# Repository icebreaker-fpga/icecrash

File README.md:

# iCECrash

The Retro game console and demoscene motherboard for iCEBreaker-bitsy.

This project has moved to [Codeberg](https://codeberg.org/icebreaker-fpga/icecrash)

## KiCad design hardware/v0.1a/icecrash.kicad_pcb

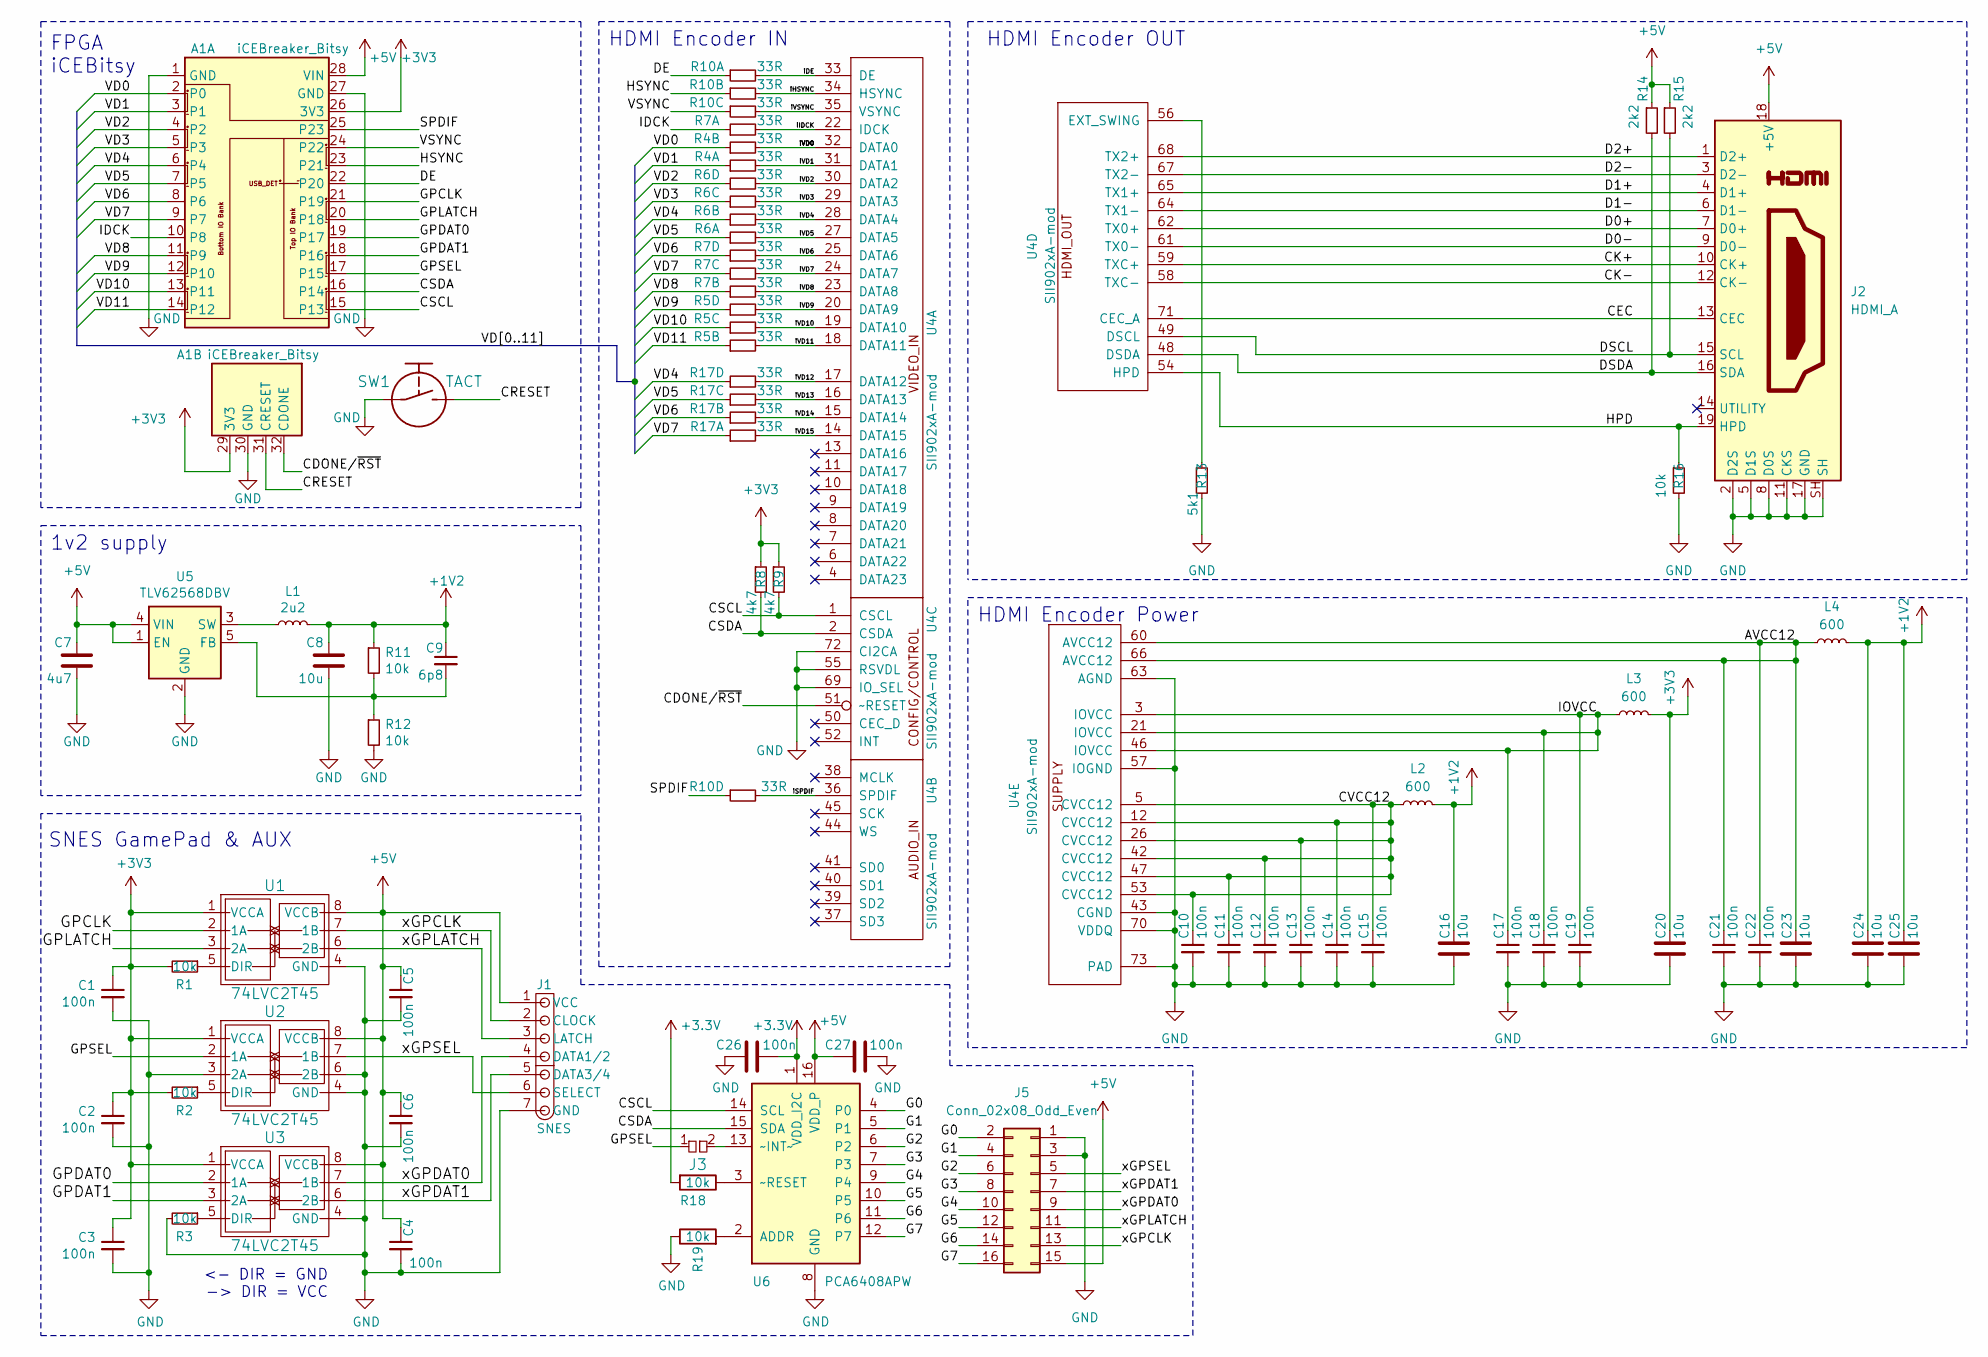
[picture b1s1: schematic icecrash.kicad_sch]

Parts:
A1: iCEBreaker_Bitsy
C1, C2, C3, C4, C5, C6, C10, C11, C12, C13, C14, C15, C17, C18, C19, C21, C22: 100n; C_0402
C7: 4u7; C_0603
C8, C16, C20, C23, C24, C25: 10u; C_0603
C9: 6p8; C_0402
C26, C27: 100n; C_0402_1005Metric; MPN TMK105BJ104KV-F
J1: SNES
J2: HDMI_A; HDMI-10029449-111RLF
J3: pkl_jumper; J_0603
J5: Conn_02x08_Odd_Even; PinHeader_2x08_P2.54mm_Horizontal
L1: 2u2; L_0805
L2, L3, L4: 600; L_0402
R1, R2, R3, R11, R12, R16: 10k; R_0402
R4, R5, R6, R7, R10, R17: 33R; R_Array_Convex_4x0402
R8, R9: 4k7; R_0402
R13: 5k1; R_0402
R14, R15: 2k2; R_0402
R18, R19: 10k; R_0402_1005Metric; MPN RC0402FR-1310KL
SW1: TACT; SW_SPST_3x4x2.5
U1, U2, U3: 74LVC2T45; SOT-833-1
U4: SII902xA-mod; QFN-72-1EP_10x10mm_P0.5mm_EP6x6mm_ThermalVias
U5: TLV62568DBV; SOT-23-5
U6: PCA6408APW; TSSOP-16_4.4x5mm_P0.65mm; MPN PCA6408APW

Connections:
+1V2: C8.1, C9.1, C16.1, C24.1, C25.1, L1.1, L2.1, L4.1, R11.1
+5V: A1.28 (VIN), C4.1, C5.1, C6.1, C7.1, C27.1, J1.1 (VCC), J2.18 (+5V), J5.15, R14.1, R15.1, U1.8 (VCCB), U2.8 (VCCB), U3.8 (VCCB), U5.1 (EN), U5.4 (VIN), U6.16 (VDD_P)
/AVCC12: C21.1, C22.1, C23.1, L4.2, U4.60 (AVCC12), U4.66 (AVCC12)
/CDONE/~RST: A1.32 (CDONE), U4.51 (~RESET)
/CEC: J2.13 (CEC), U4.71 (CEC_A)
/CK+: J2.10 (CK+), U4.59 (TXC+)
/CK-: J2.12 (CK-), U4.58 (TXC-)
/CRESET: A1.31 (CRESET), SW1.2
/CSCL: A1.15 (P13), R9.2, U4.1 (CSCL), U6.14 (SCL)
/CSDA: A1.16 (P14), R8.2, U4.2 (CSDA), U6.15 (SDA)
/CVCC12: C10.1, C11.1, C12.1, C13.1, C14.1, C15.1, L2.2, U4.5 (CVCC12), U4.12 (CVCC12), U4.26 (CVCC12), U4.42 (CVCC12), U4.47 (CVCC12), U4.53 (CVCC12)
/D0+: J2.7 (D0+), U4.62 (TX0+)
/D0-: J2.9 (D0-), U4.61 (TX0-)
/D1+: J2.4 (D1+), U4.65 (TX1+)
/D1-: J2.6 (D1-), U4.64 (TX1-)
/D2+: J2.1 (D2+), U4.68 (TX2+)
/D2-: J2.3 (D2-), U4.67 (TX2-)
/DE: A1.22 (P20), R10.1
/DSCL: J2.15 (SCL), R15.2, U4.49 (DSCL)
/DSDA: J2.16 (SDA), R14.2, U4.48 (DSDA)
/G0: J5.2, U6.4 (P0)
/G1: J5.4, U6.5 (P1)
/G2: J5.6, U6.6 (P2)
/G3: J5.8, U6.7 (P3)
/G4: J5.10, U6.9 (P4)
/G5: J5.12, U6.10 (P5)
/G6: J5.14, U6.11 (P6)
/G7: J5.16, U6.12 (P7)
/GPCLK: A1.21 (P19), U1.2 (1A)
/GPDAT0: A1.19 (P17), U3.2 (1A)
/GPDAT1: A1.18 (P16), U3.3 (2A)
/GPLATCH: A1.20 (P18), U1.3 (2A)
/GPSEL: A1.17 (P15), J3.1, U2.2 (1A)
/HPD: J2.19 (HPD), R16.1, U4.54 (HPD)
/HSYNC: A1.23 (P21), R10.3
/IDCK: A1.10 (P8), R7.1
/IOVCC: C17.1, C18.1, C19.1, L3.2, U4.3 (IOVCC), U4.21 (IOVCC), U4.46 (IOVCC)
/SPDIF: A1.25 (P23), R10.7
/VD0: A1.2 (P0), R4.3
/VD1: A1.3 (P1), R4.1
/VD2: A1.4 (P2), R6.7
/VD3: A1.5 (P3), R6.5
/VD4: A1.6 (P4), R6.3, R17.7
/VD5: A1.7 (P5), R6.1, R17.5
/VD6: A1.8 (P6), R7.7, R17.3
/VD7: A1.9 (P7), R7.5, R17.1
/VD8: A1.11 (P9), R7.3
/VD9: A1.12 (P10), R5.7
/VD10: A1.13 (P11), R5.5
/VD11: A1.14 (P12), R5.3
/VSYNC: A1.24 (P22), R10.5
/iDE: R10.2, U4.33 (DE)
/iHSYNC: R10.4, U4.34 (HSYNC)
/iIDCK: R7.2, U4.22 (IDCK)
/iSPDIF: R10.8, U4.36 (SPDIF)
/iVD0: R4.4, U4.32 (DATA0)
/iVD1: R4.2, U4.31 (DATA1)
/iVD2: R6.8, U4.30 (DATA2)
/iVD3: R6.6, U4.29 (DATA3)
/iVD4: R6.4, U4.28 (DATA4)
/iVD5: R6.2, U4.27 (DATA5)
/iVD6: R7.8, U4.25 (DATA6)
/iVD7: R7.6, U4.24 (DATA7)
/iVD8: R7.4, U4.23 (DATA8)
/iVD9: R5.8, U4.20 (DATA9)
/iVD10: R5.6, U4.19 (DATA10)
/iVD11: R5.4, U4.18 (DATA11)
/iVD12: R17.8, U4.17 (DATA12)
/iVD13: R17.6, U4.16 (DATA13)
/iVD14: R17.4, U4.15 (DATA14)
/iVD15: R17.2, U4.14 (DATA15)
/iVSYNC: R10.6, U4.35 (VSYNC)
/xGPCLK: J1.2 (CLOCK), J5.13, U1.7 (1B)
/xGPDAT0: J1.4 (DATA1/2), J5.9, U3.7 (1B)
/xGPDAT1: J1.5 (DATA3/4), J5.7, U3.6 (2B)
/xGPLATCH: J1.3 (LATCH), J5.11, U1.6 (2B)
/xGPSEL: J1.6 (SELECT), J5.5, U2.7 (1B)
GND: A1.1 (GND), A1.27 (GND), A1.30 (GND), C1.2, C2.2, C3.2, C4.2, C5.2, C6.2, C7.2, C8.2, C10.2, C11.2, C12.2, C13.2, C14.2, C15.2, C16.2, C17.2, C18.2, C19.2, C20.2, C21.2, C22.2, C23.2, C24.2, C25.2, C26.2, C27.2, J1.7 (GND), J2.2 (D2S), J2.5 (D1S), J2.8 (D0S), J2.11 (CKS), J2.17 (GND), J2.SH, J5.1, J5.3, R3.2, R12.2, R13.2, R16.2, R19.1, SW1.1, U1.4 (GND), U2.3 (2A), U2.4 (GND), U2.6 (2B), U3.4 (GND), U4.43 (CGND), U4.55 (RSVDL), U4.57 (IOGND), U4.63 (AGND), U4.69 (IO_SEL), U4.70 (VDDQ), U4.72 (CI2CA), U4.73 (PAD), U5.2 (GND), U6.8 (GND)
unnamed: C9.2, R11.2, R12.1, U5.5 (FB)
unnamed: J3.2, U6.13 (~INT~)
unnamed: L1.2, U5.3 (SW)
unnamed: R1.1, U1.5 (DIR)
unnamed: R2.1, U2.5 (DIR)
unnamed: R3.1, U3.5 (DIR)
unnamed: R13.1, U4.56 (EXT_SWING)
unnamed: R18.1, U6.3 (~RESET)
unnamed: R19.2, U6.2 (ADDR)

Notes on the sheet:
FPGA iCEBitsy
1v2 supply
SNES GamePad & AUX
<- DIR = GND -> DIR = VCC
HDMI Encoder IN
HDMI Encoder Power
HDMI Encoder OUT

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
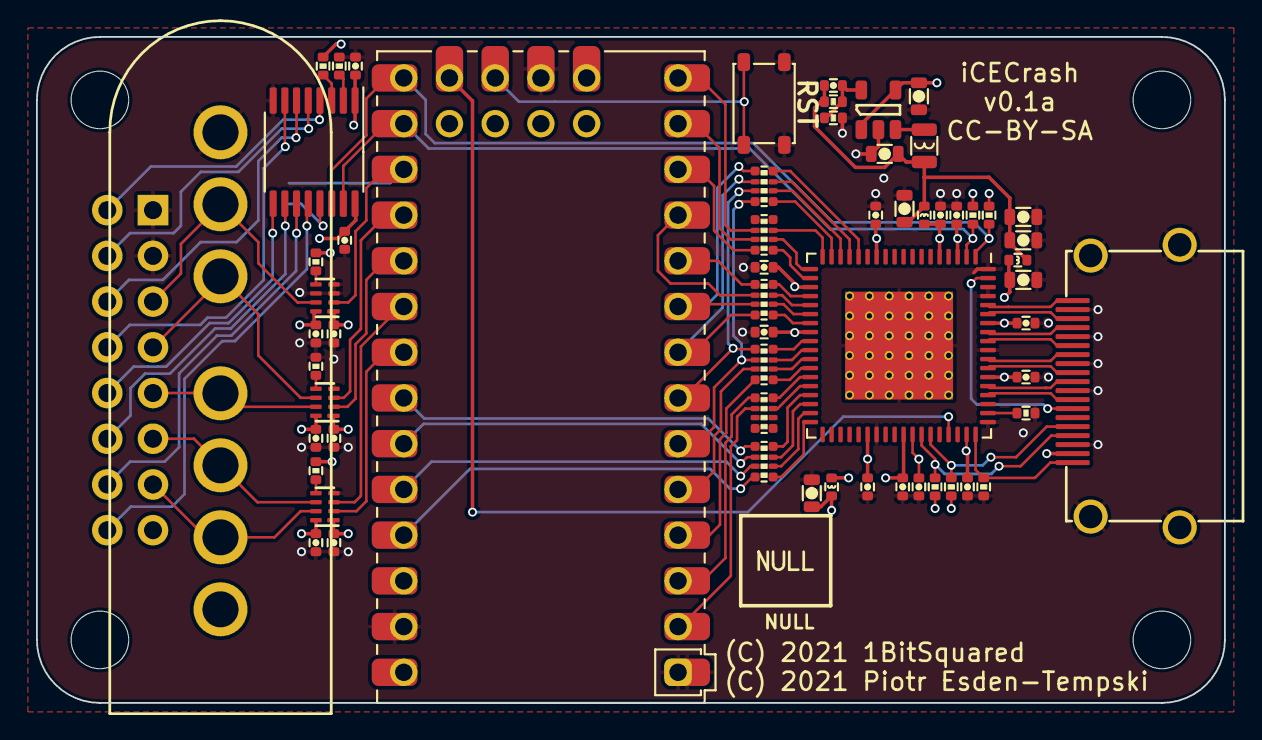
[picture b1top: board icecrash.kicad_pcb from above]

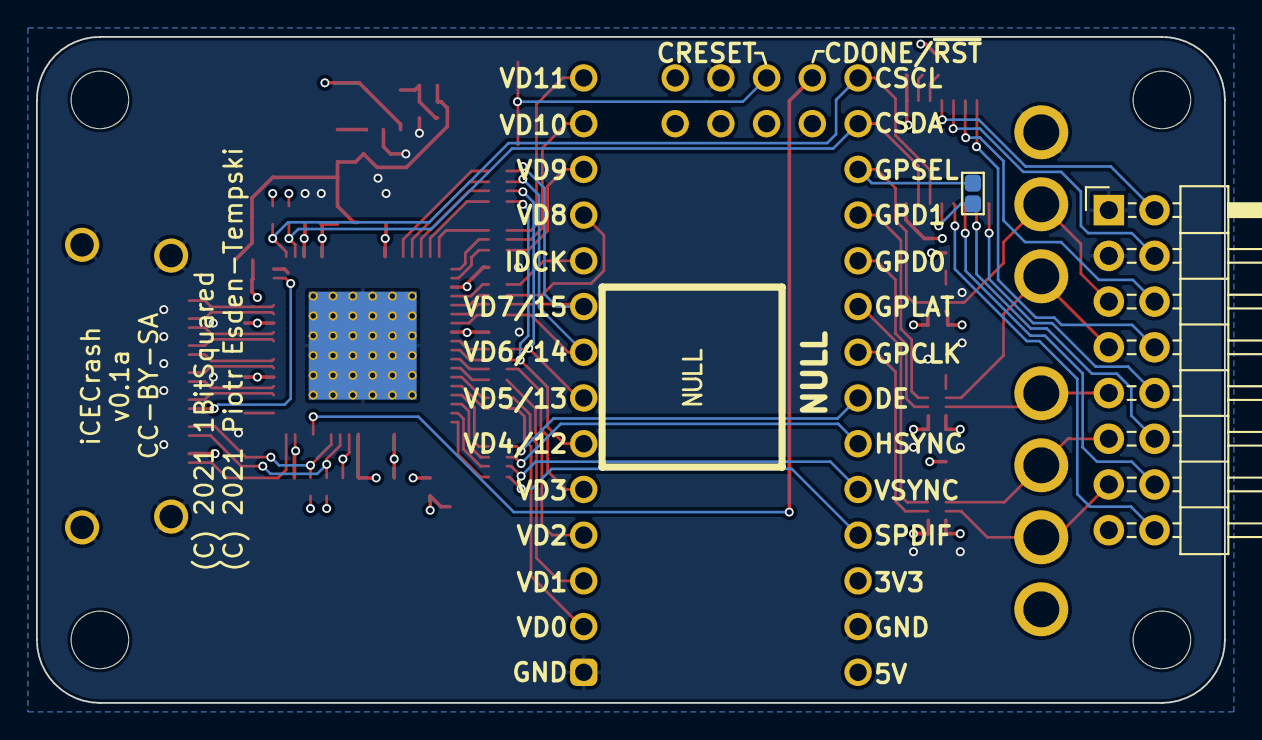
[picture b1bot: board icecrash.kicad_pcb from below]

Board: 4 copper layers, 66.0 x 37.0 mm, 62 parts (2 on the bottom side), 88 nets.

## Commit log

2021-07-07 Initial commit.
2021-07-08 Added schematic PDF.
2021-07-16 Updated PKL.
2021-07-16 First draft of the schematic.
    Connected all the remaining pins of the encoder chip.
    Replaced the SNES connector generic symbol with a dedicated one.
    Added ESD protection to the HDMI connector. (might delete later ;) )
    Added level shifters for the SNES interface.
2021-07-16 Removed ESD protection. It is a toy after all...
    * I think it is worth saving $4 over the ESD protection in this case.
    Also updated the schematic PDF.
2021-07-23 Improved schematic and started layout.
    * Added inline termination resistors.
    * Corrected a mistake in the encoder symbol.
    (Pin 15/13 and missing Pin 70)
    * Preliminary positioning of the parts on the PCB.
    * Started routing the input data pins.
2021-07-28 First routing pass.
    State after Electronics Let's Play stream.
2021-08-11 Improved layout from Aug 10th stream.
    Added GPIO expander and AUX connector.
    Compressed board a bit.
2021-08-11 Renamed project to iCECrash.
2021-08-13 Changed the HDMI encoder wiring a bit.
    It is better to leave the sync signals alone. We can double assign some
    of the data pins to gain access to a bunch of additional video data
    modes. Now `d[7:4]` are also connected to `d[15:12]`.
2021-08-14 More compression work. Fixed a few bugs, added silkscreen.
2021-08-17 Aligned pin headers to the PCB center.
2021-08-17 Updated copper fills.
2026-05-24 We have moved to Codeberg see README.

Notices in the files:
hardware/v0.1a/icecrash.kicad_pcb:
(C) 2021 1BitSquared
(C) 2021 Piotr Esden-Tempski
License: CC-BY-SA
CC-BY-SA
